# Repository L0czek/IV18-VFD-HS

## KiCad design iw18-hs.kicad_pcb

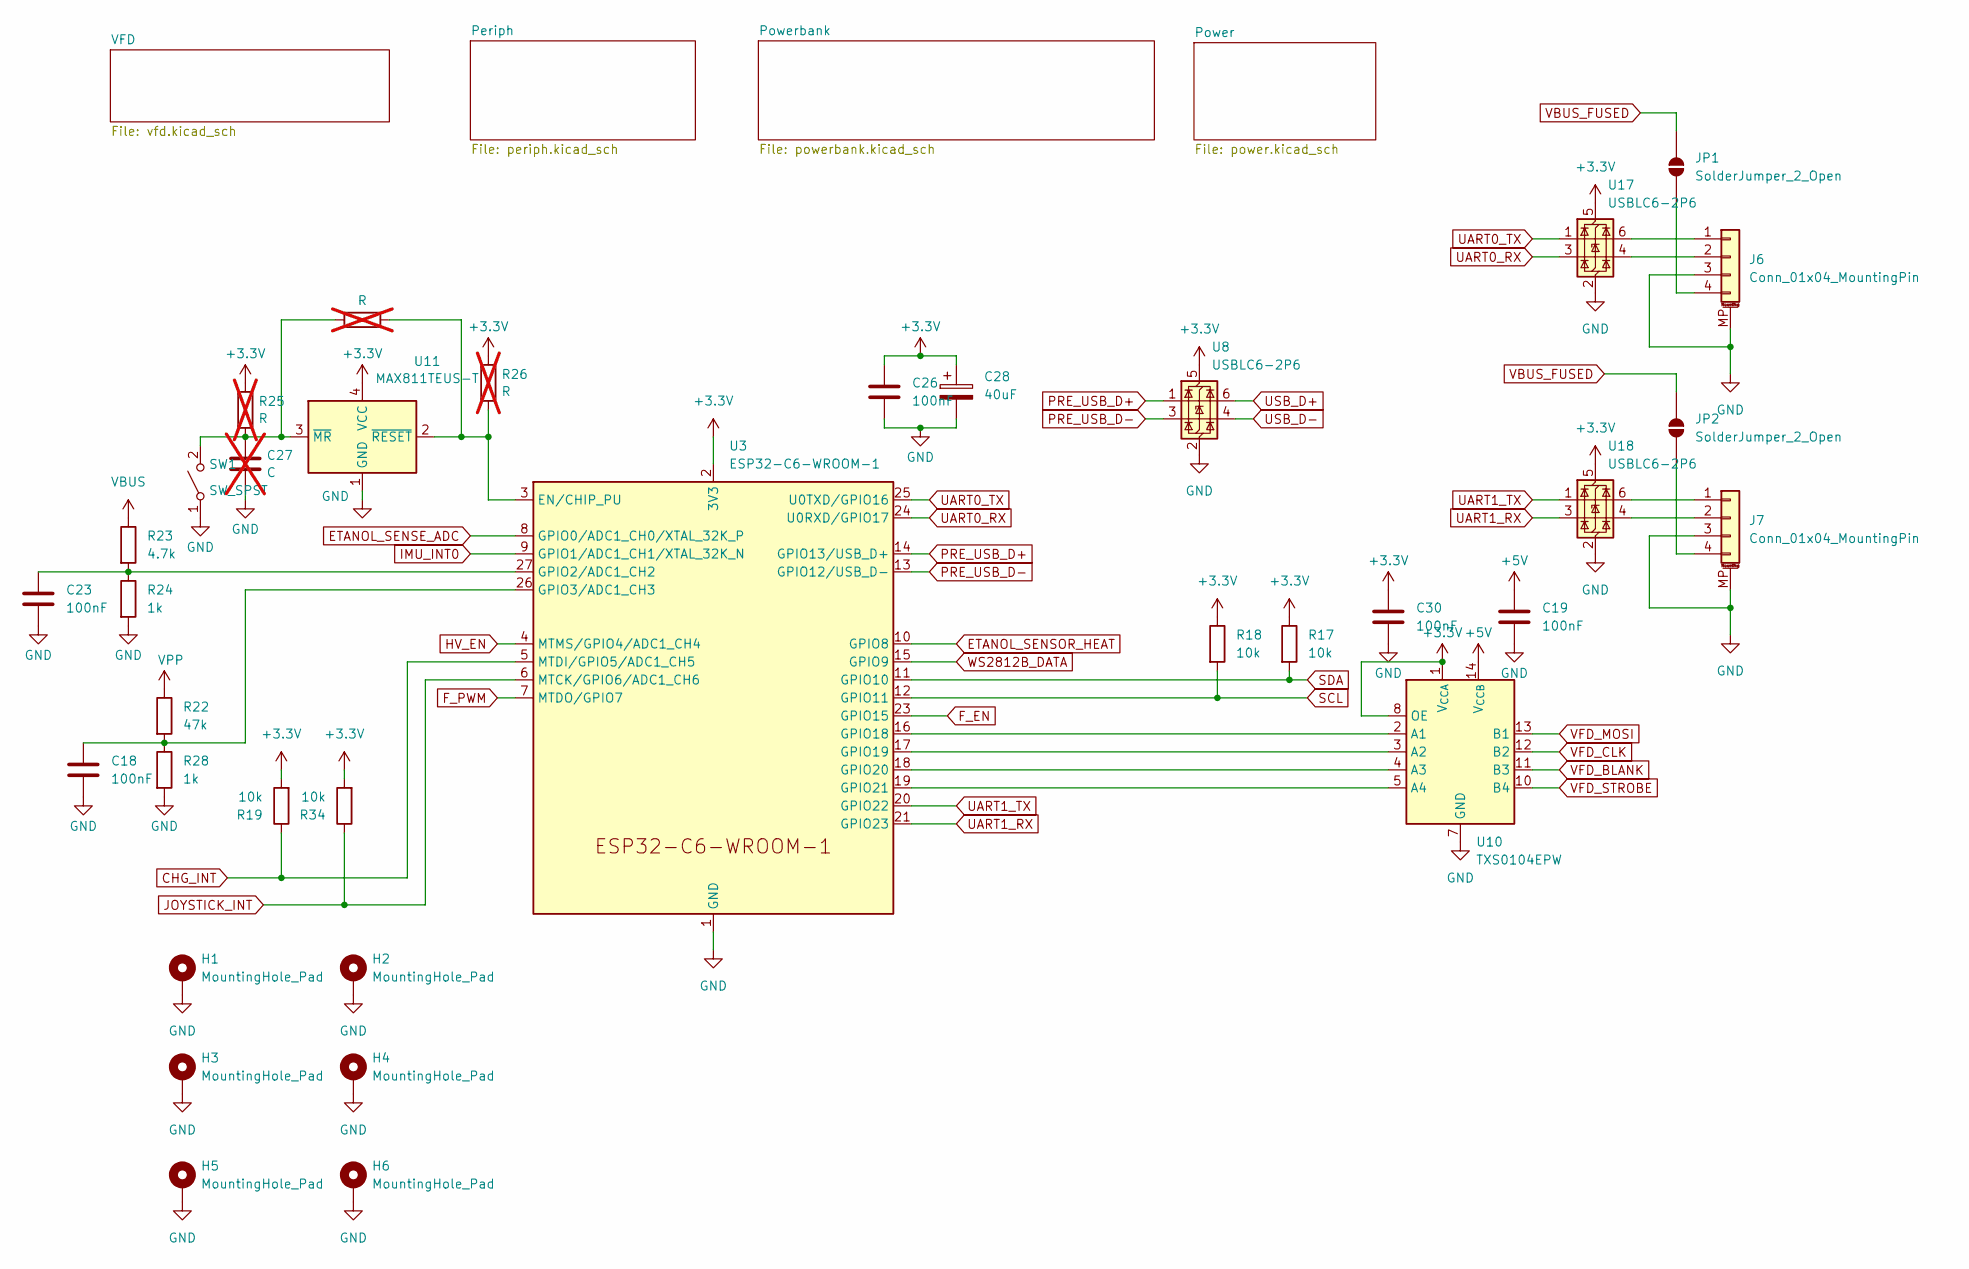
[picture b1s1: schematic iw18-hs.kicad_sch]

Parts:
C18, C19, C23, C26, C30: 100nF; C_0805_2012Metric
C27: C; C_0805_2012Metric; not fitted
C28: 40uF; CP_EIA-7343-31_Kemet-D
H1, H2: MountingHole_Pad; MountingHole_4.3mm_M4_Pad_Via
H3, H4, H5, H6: MountingHole_Pad; MountingHole_2.2mm_M2_Pad_Via
J6, J7: Conn_01x04_MountingPin; JST_PH_S4B-PH-SM4-TB_1x04-1MP_P2.00mm_Horizontal
JP1, JP2: SolderJumper_2_Open; SolderJumper-2_P1.3mm_Open_RoundedPad1.0x1.5mm
R7, R25, R26: R; R_0805_2012Metric; not fitted
R17, R18, R19, R34: 10k; R_0805_2012Metric
R22: 47k; R_0805_2012Metric
R23: 4.7k; R_0805_2012Metric
R24, R28: 1k; R_0805_2012Metric
SW1: SW_SPST; SW_SPST_B3S-1000
U3: ESP32-C6-WROOM-1
U8, U17, U18: USBLC6-2P6; SOT-666
U10: TXS0104EPW; TSSOP-14_4.4x5mm_P0.65mm
U11: MAX811TEUS-T; SOT-143

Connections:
+3.3V: C26.1, C28.1, C30.1, R17.1, R18.1, R19.2, R25.1, R26.1, R34.2, U3.2 (3V3), U8.5 (VBUS), U10.1 (V_{CCA}), U10.8 (OE), U11.4 (VCC), U17.5 (VBUS), U18.5 (VBUS); also elsewhere on the board
+5V: C19.1, U10.14 (V_{CCB}); also elsewhere on the board
CHG_INT: R19.1, U3.5 (MTDI/GPIO5/ADC1_CH5); also elsewhere on the board
ETANOL_SENSE_ADC: U3.8 (GPIO0/ADC1_CH0/XTAL_32K_P); also elsewhere on the board
ETANOL_SENSOR_HEAT: U3.10 (GPIO8); also elsewhere on the board
F_EN: U3.23 (GPIO15); also elsewhere on the board
F_PWM: U3.7 (MTDO/GPIO7); also elsewhere on the board
GND: C18.2, C19.2, C23.2, C26.2, C27.2, C28.2, C30.2, H1.1 (1_1), H2.1 (1_1), H3.1 (1_1), H4.1 (1_1), H5.1 (1_1), H6.1 (1_1), J6.3, J6.MP (MountPin), J7.3, J7.MP (MountPin), R24.2, R28.2, SW1.1 (A), U3.1 (GND), U3.28 (GND), U3.29 (GND), U8.2 (GND), U10.7 (GND), U11.1 (GND), U17.2 (GND), U18.2 (GND); also elsewhere on the board
HV_EN: U3.4 (MTMS/GPIO4/ADC1_CH4); also elsewhere on the board
IMU_INT0: U3.9 (GPIO1/ADC1_CH1/XTAL_32K_N); also elsewhere on the board
JOYSTICK_INT: R34.1, U3.6 (MTCK/GPIO6/ADC1_CH6); also elsewhere on the board
unnamed: J6.1, U17.6 (I/O1)
unnamed: J6.2, U17.4 (I/O2)
unnamed: J6.4, JP1.1 (A)
unnamed: J7.1, U18.6 (I/O1)
unnamed: J7.2, U18.4 (I/O2)
unnamed: J7.4, JP2.1 (A)
unnamed: C27.1, R7.1, R25.2, SW1.2 (B), U11.3 (~MR)
unnamed: C23.1, R23.2, R24.1, U3.27 (GPIO2/ADC1_CH2)
unnamed: C18.1, R22.2, R28.1, U3.26 (GPIO3/ADC1_CH3)
unnamed: U3.16 (GPIO18), U10.2 (A1)
unnamed: U3.17 (GPIO19), U10.3 (A2)
unnamed: U3.18 (GPIO20), U10.4 (A3)
unnamed: U3.19 (GPIO21), U10.5 (A4)
unnamed: R7.2, R26.2, U3.3 (EN/CHIP_PU), U11.2 (~RESET)
PRE_USB_D+: U3.14 (GPIO13/USB_D+), U8.1 (I/O1)
PRE_USB_D-: U3.13 (GPIO12/USB_D-), U8.3 (I/O2)
SCL: R18.2, U3.12 (GPIO11); also elsewhere on the board
SDA: R17.2, U3.11 (GPIO10); also elsewhere on the board
UART0_RX: U3.24 (U0RXD/GPIO17), U17.3 (I/O2)
UART0_TX: U3.25 (U0TXD/GPIO16), U17.1 (I/O1)
UART1_RX: U3.21 (GPIO23), U18.3 (I/O2)
UART1_TX: U3.20 (GPIO22), U18.1 (I/O1)
USB_D+: U8.6 (I/O1); also elsewhere on the board
USB_D-: U8.4 (I/O2); also elsewhere on the board
VBUS: R23.1; also elsewhere on the board
VBUS_FUSED: JP1.2 (B), JP2.2 (B); also elsewhere on the board
VFD_BLANK: U10.11 (B3); also elsewhere on the board
VFD_CLK: U10.12 (B2); also elsewhere on the board
VFD_MOSI: U10.13 (B1); also elsewhere on the board
VFD_STROBE: U10.10 (B4); also elsewhere on the board
VPP: R22.1; also elsewhere on the board
WS2812B_DATA: U3.15 (GPIO9); also elsewhere on the board

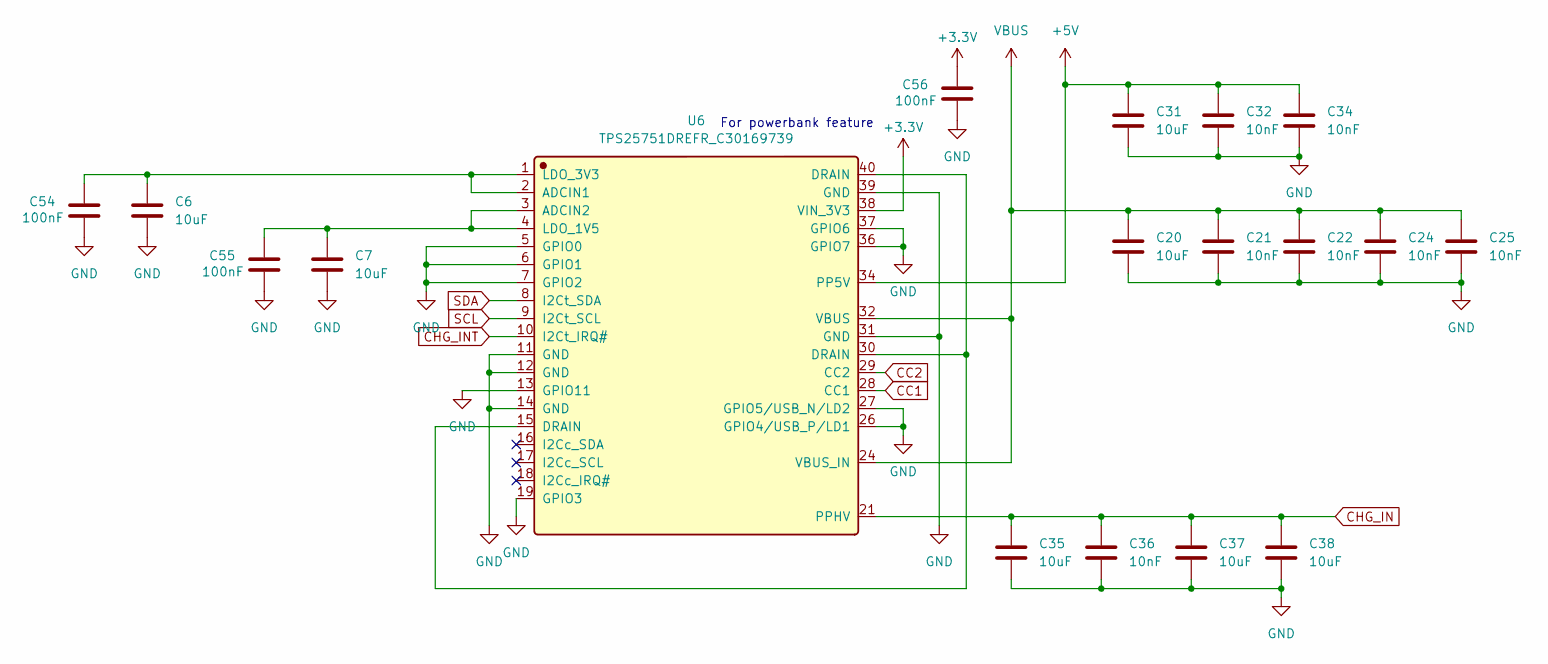
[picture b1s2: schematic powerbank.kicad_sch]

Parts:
C6, C7, C20, C31, C35, C37, C38: 10uF; C_0805_2012Metric
C21, C22, C24, C25, C32, C34: 10nF; C_0402_1005Metric
C36: 10nF; C_0805_2012Metric
C54, C55, C56: 100nF; C_0402_1005Metric
U6: TPS25751DREFR_C30169739; Manufacturer Part TPS25751DREFR; LCSC C30169739

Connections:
+3.3V: C56.1, U6.38 (VIN_3V3); also elsewhere on the board
+5V: C31.1, C32.1, C34.1, U6.34 (PP5V); also elsewhere on the board
CC1: U6.28 (CC1); also elsewhere on the board
CC2: U6.29 (CC2); also elsewhere on the board
CHG_IN: C35.1, C36.1, C37.1, C38.1, U6.21 (PPHV); also elsewhere on the board
CHG_INT: U6.10 (I2Ct_IRQ#); also elsewhere on the board
GND: C6.2, C7.2, C20.2, C21.2, C22.2, C24.2, C25.2, C31.2, C32.2, C34.2, C35.2, C36.2, C37.2, C38.2, C54.2, C55.2, C56.2, U6.5 (GPIO0), U6.6 (GPIO1), U6.7 (GPIO2), U6.11 (GND), U6.12 (GND), U6.13 (GPIO11), U6.14 (GND), U6.19 (GPIO3), U6.26 (GPIO4/USB_P/LD1), U6.27 (GPIO5/USB_N/LD2), U6.31 (GND), U6.36 (GPIO7), U6.37 (GPIO6), U6.39 (GND); also elsewhere on the board
unnamed: C6.1, C54.1, U6.1 (LDO_3V3), U6.2 (ADCIN1)
unnamed: C7.1, C55.1, U6.3 (ADCIN2), U6.4 (LDO_1V5)
unnamed: U6.15 (DRAIN), U6.30 (DRAIN), U6.40 (DRAIN)
SCL: U6.9 (I2Ct_SCL); also elsewhere on the board
SDA: U6.8 (I2Ct_SDA); also elsewhere on the board
VBUS: C20.1, C21.1, C22.1, C24.1, C25.1, U6.24 (VBUS_IN), U6.32 (VBUS); also elsewhere on the board

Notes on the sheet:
For powerbank feature

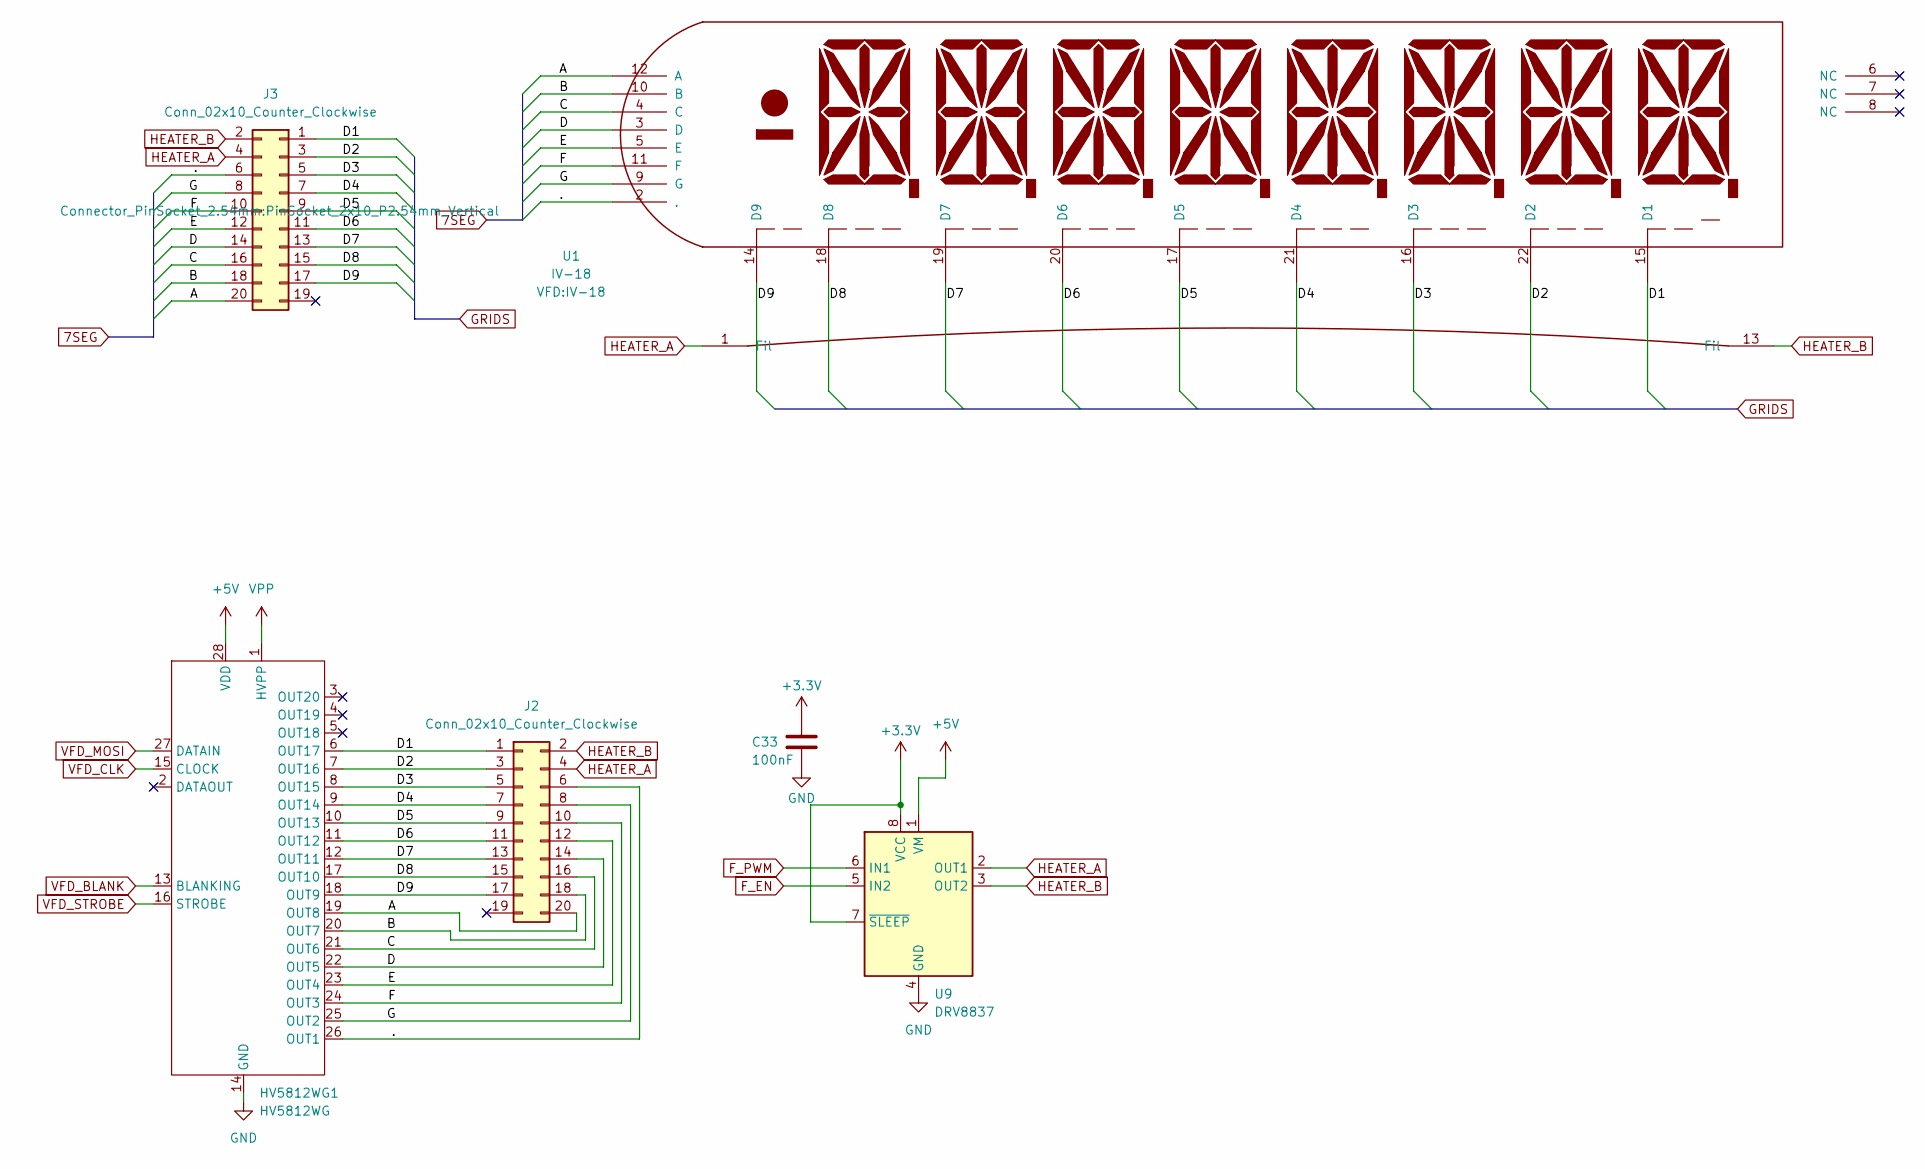
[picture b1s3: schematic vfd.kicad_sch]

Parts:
C33: 100nF; C_0805_2012Metric
HV5812WG1: HV5812WG; SOIC-28W_7.5x17.9mm_P1.27mm
J2: Conn_02x10_Counter_Clockwise; PinHeader_2x10_P2.54mm_Vertical
J3: Conn_02x10_Counter_Clockwise; PinSocket_2x10_P2.54mm_Vertical
U1: IV-18
U9: DRV8837; WSON-8-1EP_2x2mm_P0.5mm_EP0.9x1.6mm

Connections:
+3.3V: C33.1, U9.7 (~SLEEP), U9.8 (VCC); also elsewhere on the board
+5V: HV5812WG1.28 (VDD), U9.1 (VM); also elsewhere on the board
/VFD/.: HV5812WG1.26 (OUT1), J2.6, J3.6, U1.2 (.)
/VFD/A: HV5812WG1.19 (OUT8), J2.20, J3.20, U1.12 (A)
/VFD/B: HV5812WG1.20 (OUT7), J2.18, J3.18, U1.10 (B)
/VFD/C: HV5812WG1.21 (OUT6), J2.16, J3.16, U1.4 (C)
/VFD/D: HV5812WG1.22 (OUT5), J2.14, J3.14, U1.3 (D)
/VFD/D1: HV5812WG1.6 (OUT17), J2.1, J3.1, U1.15 (D1)
/VFD/D2: HV5812WG1.7 (OUT16), J2.3, J3.3, U1.22 (D2)
/VFD/D3: HV5812WG1.8 (OUT15), J2.5, J3.5, U1.16 (D3)
/VFD/D4: HV5812WG1.9 (OUT14), J2.7, J3.7, U1.21 (D4)
/VFD/D5: HV5812WG1.10 (OUT13), J2.9, J3.9, U1.17 (D5)
/VFD/D6: HV5812WG1.11 (OUT12), J2.11, J3.11, U1.20 (D6)
/VFD/D7: HV5812WG1.12 (OUT11), J2.13, J3.13, U1.19 (D7)
/VFD/D8: HV5812WG1.17 (OUT10), J2.15, J3.15, U1.18 (D8)
/VFD/D9: HV5812WG1.18 (OUT9), J2.17, J3.17, U1.14 (D9)
/VFD/E: HV5812WG1.23 (OUT4), J2.12, J3.12, U1.5 (E)
/VFD/F: HV5812WG1.24 (OUT3), J2.10, J3.10, U1.11 (F)
/VFD/G: HV5812WG1.25 (OUT2), J2.8, J3.8, U1.9 (G)
F_EN: U9.5 (IN2); also elsewhere on the board
F_PWM: U9.6 (IN1); also elsewhere on the board
GND: C33.2, HV5812WG1.14 (GND), U9.4 (GND), U9.9 (GND); also elsewhere on the board
HEATER_A: J2.4, J3.4, U1.1 (Fil), U9.2 (OUT1)
HEATER_B: J2.2, J3.2, U1.13 (Fil), U9.3 (OUT2)
VFD_BLANK: HV5812WG1.13 (BLANKING); also elsewhere on the board
VFD_CLK: HV5812WG1.15 (CLOCK); also elsewhere on the board
VFD_MOSI: HV5812WG1.27 (DATAIN); also elsewhere on the board
VFD_STROBE: HV5812WG1.16 (STROBE); also elsewhere on the board
VPP: HV5812WG1.1 (HVPP); also elsewhere on the board

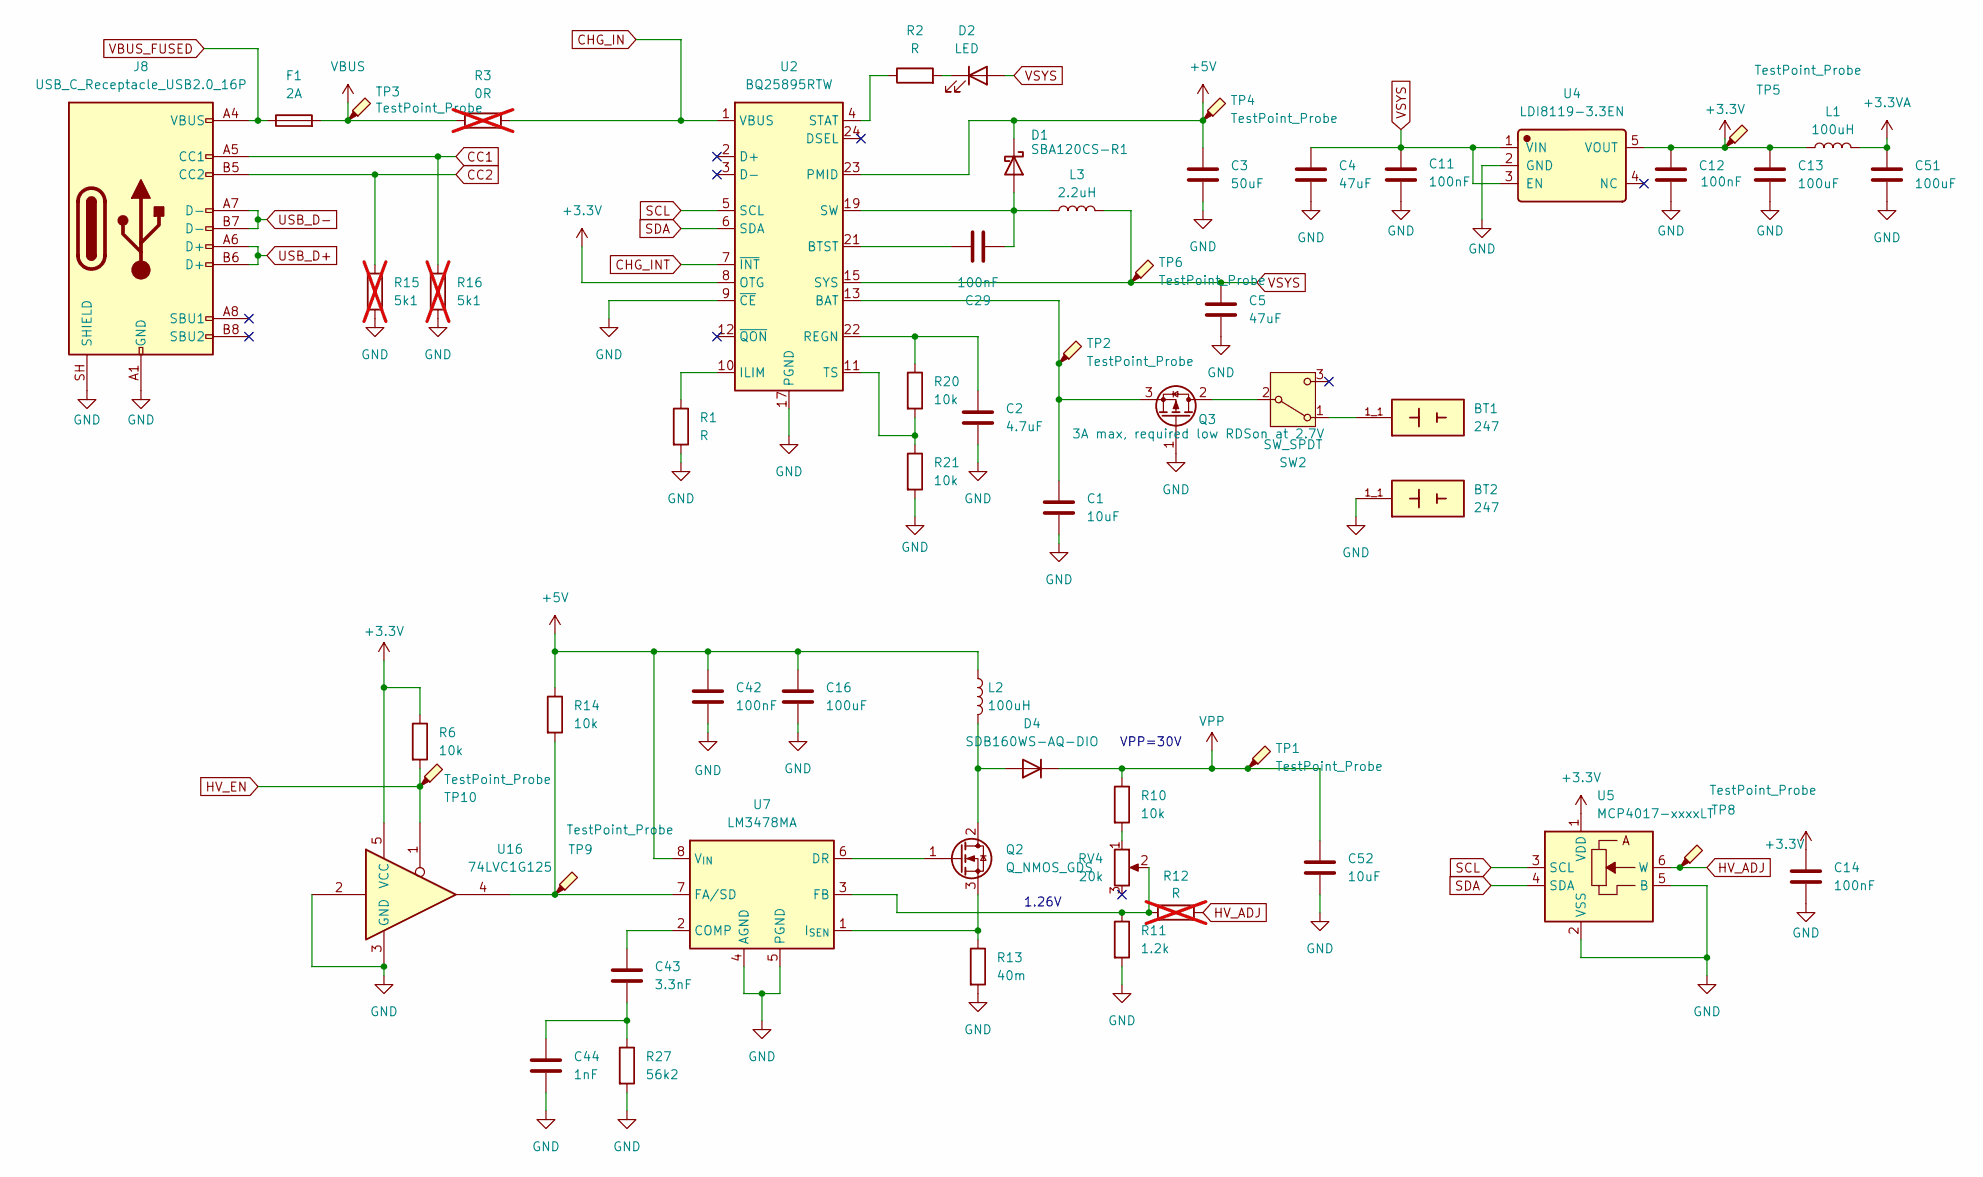
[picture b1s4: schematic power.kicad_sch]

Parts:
BT1, BT2: 247; BAT_247; PARTREV A
C1: 10uF; C_0805_2012Metric
C2: 4.7uF; C_0805_2012Metric
C3: 50uF; C_0805_2012Metric
C4, C5: 47uF; C_0805_2012Metric
C11, C12, C14, C29, C42: 100nF; C_0805_2012Metric
C13, C16, C51: 100uF; C_1206_3216Metric
C43: 3.3nF; C_0805_2012Metric
C44: 1nF; C_0805_2012Metric
C52: 10uF; C_1206_3216Metric
D1: SBA120CS-R1; D_SOD-323
D2: LED; LED_0805_2012Metric
D4: SDB160WS-AQ-DIO; D_SOD-323
F1: 2A; Fuse_0805_2012Metric
J8: USB_C_Receptacle_USB2.0_16P; USB_C_Receptacle_G-Switch_GT-USB-7010ASV
L1: 100uH; L_0805_2012Metric
L2: 100uH; L_Bourns_SRP1038C_10.0x10.0mm
L3: 2.2uH; L_Taiyo-Yuden_NR-50xx
Q2: Q_NMOS_GDS; TO-252-3_TabPin2
Q3: 3A max, required low RDSon at 2.7V; SOT-23
R1, R2: R; R_0805_2012Metric
R3: 0R; R_0805_2012Metric; not fitted
R6, R10, R14, R20, R21: 10k; R_0805_2012Metric
R11: 1.2k; R_0805_2012Metric
R12: R; R_0805_2012Metric; not fitted
R13: 40m; R_0805_2012Metric
R15, R16: 5k1; R_0805_2012Metric; not fitted
R27: 56k2; R_0805_2012Metric
RV4: 20k; Potentiometer_Bourns_3269W_Vertical
SW2: SW_SPDT; SW_SPDT_CK_JS102011SAQN
TP1, TP3, TP4, TP5, TP6: TestPoint_Probe; TestPoint_THTPad_D2.0mm_Drill1.0mm
TP2: TestPoint_Probe; TestPoint_Pad_D2.0mm
TP8, TP9, TP10: TestPoint_Probe; TestPoint_Pad_D1.0mm
U2: BQ25895RTW; Texas_RTW_WQFN-24-1EP_4x4mm_P0.5mm_EP2.7x2.7mm_ThermalVias
U4: LDI8119-3.3EN; LDI8119-3_3EN; Manufacturer Part LDI8119-3.3EN; LCSC C6079055
U5: MCP4017-xxxxLT; SOT-363_SC-70-6
U7: LM3478MA; SOIC-8_3.9x4.9mm_P1.27mm
U16: 74LVC1G125; Texas_R-PDSO-G5_DCK-5

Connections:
+3.3V: C12.1, C13.1, C14.1, L1.1, R6.1, TP5.1 (1_1), U2.8 (OTG), U4.5 (VOUT), U5.1 (VDD), U16.5 (VCC); also elsewhere on the board
+3.3VA: C51.1, L1.2; also elsewhere on the board
+5V: C3.1, C16.1, C42.1, D1.1 (K), L2.1, R14.1, TP4.1 (1_1), U2.23 (PMID), U7.8 (V_{IN}); also elsewhere on the board
CC1: J8.A5 (CC1), R16.1; also elsewhere on the board
CC2: J8.B5 (CC2), R15.1; also elsewhere on the board
CHG_IN: R3.2, U2.1 (VBUS); also elsewhere on the board
CHG_INT: U2.7 (~INT); also elsewhere on the board
GND: BT2.1_1, BT2.1_2, BT2.1_3, C1.2, C2.2, C3.2, C4.2, C5.2, C11.2, C12.2, C13.2, C14.2, C16.2, C42.2, C44.2, C51.2, C52.2, J8.A1 (GND), J8.A12 (GND), J8.B1 (GND), J8.B12 (GND), J8.SH (SHIELD), Q3.1 (G), R1.2, R11.2, R13.2, R15.2, R16.2, R21.2, R27.2, U2.9 (~CE), U2.17 (PGND), U2.18 (PGND), U2.25 (PGND), U4.2 (GND), U5.2 (VSS), U5.5 (B), U7.4 (AGND), U7.5 (PGND), U16.2, U16.3 (GND); also elsewhere on the board
HV_ADJ: R12.2, TP8.1 (1_1), U5.6 (W)
HV_EN: R6.2, TP10.1 (1_1), U16.1; also elsewhere on the board
unnamed: C43.2, C44.1, R27.1
unnamed: C29.1, D1.2 (A), L3.1, U2.19 (SW), U2.20 (SW)
unnamed: D2.1 (K), R2.2
unnamed: D4.2 (A), L2.2, Q2.2 (D)
unnamed: Q2.1 (G), U7.6 (DR)
unnamed: Q2.3 (S), R13.1, U7.1 (I_{SEN})
unnamed: Q3.2 (D), SW2.2 (B)
unnamed: C1.1, Q3.3 (S), TP2.1 (1_1), U2.13 (BAT), U2.14 (BAT)
unnamed: R10.2, RV4.1
unnamed: BT1.1_1, BT1.1_2, BT1.1_3, SW2.1 (A)
unnamed: C29.2, U2.21 (BTST)
unnamed: R1.1, U2.10 (ILIM)
unnamed: C2.1, R20.1, U2.22 (REGN)
unnamed: R2.1, U2.4 (STAT)
unnamed: R20.2, R21.1, U2.11 (TS)
unnamed: C43.1, U7.2 (COMP)
unnamed: R14.2, TP9.1 (1_1), U7.7 (FA/SD), U16.4
unnamed: R11.1, R12.1, RV4.2, U7.3 (FB)
SCL: U2.5 (SCL), U5.3 (SCL); also elsewhere on the board
SDA: U2.6 (SDA), U5.4 (SDA); also elsewhere on the board
USB_D+: J8.A6 (D+), J8.B6 (D+); also elsewhere on the board
USB_D-: J8.A7 (D-), J8.B7 (D-); also elsewhere on the board
VBUS: F1.2, R3.1, TP3.1 (1_1); also elsewhere on the board
VBUS_FUSED: F1.1, J8.A4 (VBUS), J8.A9 (VBUS), J8.B4 (VBUS), J8.B9 (VBUS); also elsewhere on the board
VPP: C52.1, D4.1 (K), R10.1, TP1.1 (1_1); also elsewhere on the board
VSYS: C4.1, C5.1, C11.1, D2.2 (A), L3.2, TP6.1 (1_1), U2.15 (SYS), U2.16 (SYS), U4.1 (VIN), U4.3 (EN)

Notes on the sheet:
VPP=30V
1.26V

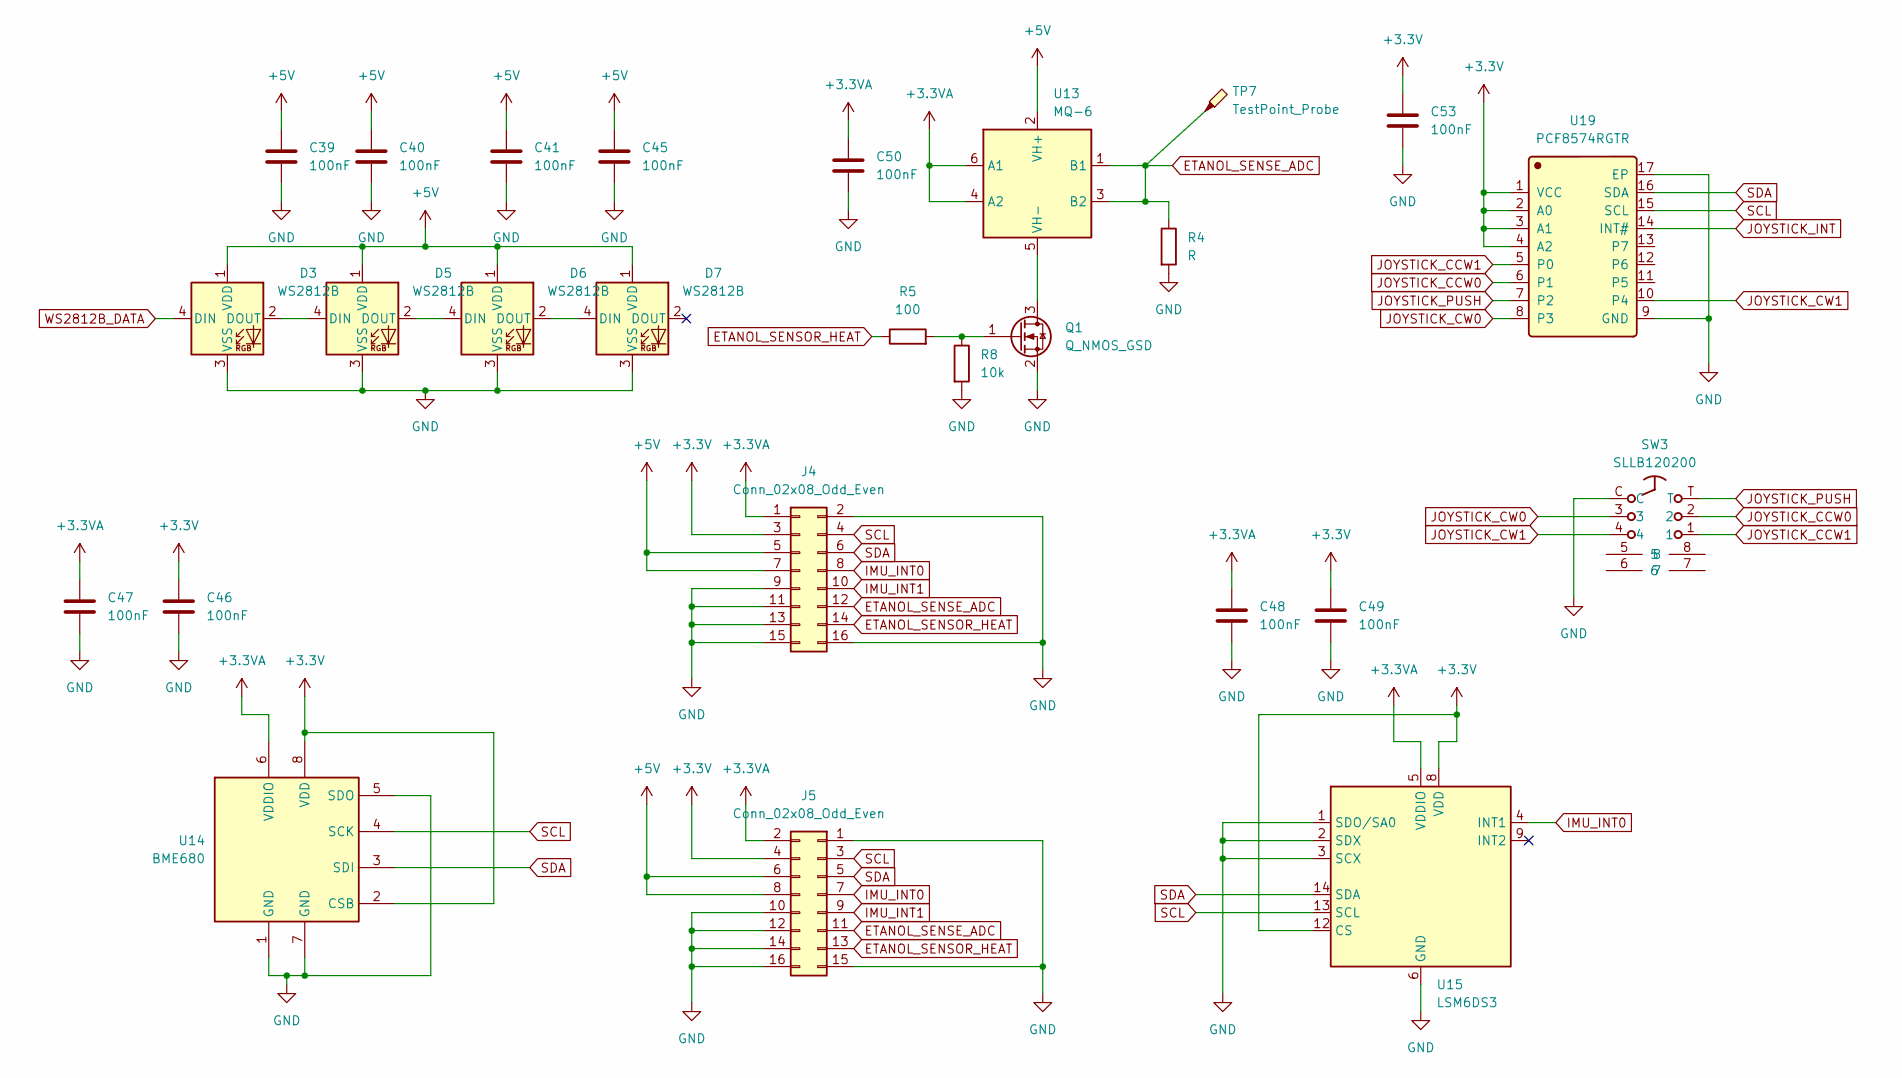
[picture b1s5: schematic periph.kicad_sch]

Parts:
C39, C40, C41, C45, C46, C47, C48, C49, C50, C53: 100nF; C_0805_2012Metric
D3, D5, D6, D7: WS2812B; LED_WS2812B_PLCC4_5.0x5.0mm_P3.2mm
J4, J5: Conn_02x08_Odd_Even; PinHeader_2x08_P2.54mm_Vertical
Q1: Q_NMOS_GSD; SOT-23
R4: R; R_0805_2012Metric
R5: 100; R_0805_2012Metric
R8: 10k; R_0805_2012Metric
SW3: SLLB120200; Manufacturer Part SLLB120200; LCSC C310813
TP7: TestPoint_Probe; TestPoint_THTPad_D2.0mm_Drill1.0mm
U13: MQ-6
U14: BME680; Bosch_LGA-8_3x3mm_P0.8mm_ClockwisePinNumbering
U15: LSM6DS3; LGA-14_3x2.5mm_P0.5mm_LayoutBorder3x4y
U19: PCF8574RGTR; WQFN-16-1EP_3x3mm_P0.5mm_EP1.6x1.6mm; Manufacturer Part PCF8574RGTR; LCSC C2652270

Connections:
+3.3V: C46.1, C49.1, C53.1, J4.3, J5.4, U14.2 (CSB), U14.8 (VDD), U15.8 (VDD), U15.12 (CS), U19.1 (VCC), U19.2 (A0), U19.3 (A1), U19.4 (A2); also elsewhere on the board
+3.3VA: C47.1, C48.1, C50.1, J4.1, J5.2, U13.4 (A2), U13.6 (A1), U14.6 (VDDIO), U15.5 (VDDIO); also elsewhere on the board
+5V: C39.1, C40.1, C41.1, C45.1, D3.1 (VDD), D5.1 (VDD), D6.1 (VDD), D7.1 (VDD), J4.5, J4.7, J5.6, J5.8, U13.2 (VH+); also elsewhere on the board
ETANOL_SENSE_ADC: J4.12, J5.11, R4.1, TP7.1 (1_1), U13.1 (B1), U13.3 (B2); also elsewhere on the board
ETANOL_SENSOR_HEAT: J4.14, J5.13, R5.1; also elsewhere on the board
GND: C39.2, C40.2, C41.2, C45.2, C46.2, C47.2, C48.2, C49.2, C50.2, C53.2, D3.3 (VSS), D5.3 (VSS), D6.3 (VSS), D7.3 (VSS), J4.2, J4.9, J4.11, J4.13, J4.15, J4.16, J5.1, J5.10, J5.12, J5.14, J5.15, J5.16, Q1.2 (S), R4.2, R8.2, SW3.C, U14.1 (GND), U14.5 (SDO), U14.7 (GND), U15.1 (SDO/SA0), U15.2 (SDX), U15.3 (SCX), U15.6 (GND), U15.7 (GND), U19.9 (GND), U19.17 (EP); also elsewhere on the board
IMU_INT0: J4.8, J5.7, U15.4 (INT1); also elsewhere on the board
IMU_INT1: J4.10, J5.9
JOYSTICK_CCW0: SW3.2, U19.6 (P1)
JOYSTICK_CCW1: SW3.1, U19.5 (P0)
JOYSTICK_CW0: SW3.3, U19.8 (P3)
JOYSTICK_CW1: SW3.4, U19.10 (P4)
JOYSTICK_INT: U19.14 (INT#); also elsewhere on the board
JOYSTICK_PUSH: SW3.T, U19.7 (P2)
unnamed: D3.2 (DOUT), D5.4 (DIN)
unnamed: D5.2 (DOUT), D6.4 (DIN)
unnamed: D6.2 (DOUT), D7.4 (DIN)
unnamed: Q1.3 (D), U13.5 (VH-)
unnamed: Q1.1 (G), R5.2, R8.1
SCL: J4.4, J5.3, U14.4 (SCK), U15.13 (SCL), U19.15 (SCL); also elsewhere on the board
SDA: J4.6, J5.5, U14.3 (SDI), U15.14 (SDA), U19.16 (SDA); also elsewhere on the board
WS2812B_DATA: D3.4 (DIN); also elsewhere on the board

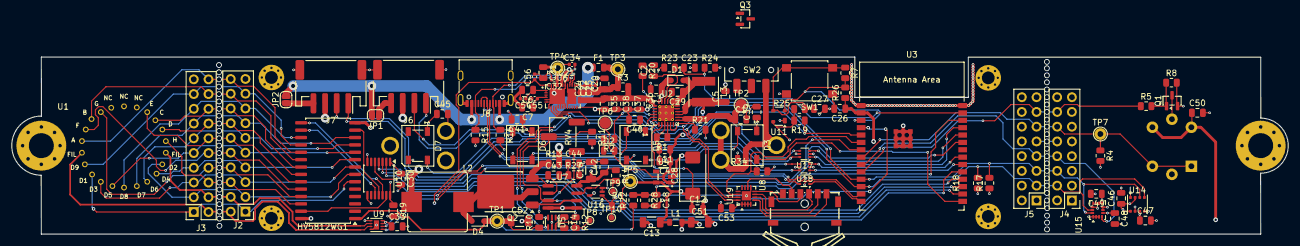
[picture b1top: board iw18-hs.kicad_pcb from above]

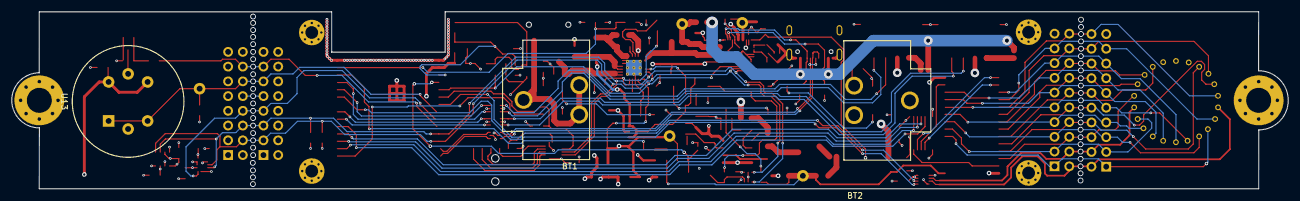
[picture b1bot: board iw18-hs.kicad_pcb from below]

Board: 4 copper layers, 220.0 x 30.5 mm, 143 parts (3 on the bottom side), 100 nets.
